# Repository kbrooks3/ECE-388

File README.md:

# ECE-388
Ping Pong Balancer Project
LCDScreen actually has all of the code included, I'm just lazy about renaming it.
If anyone wants to redefine stuff or change how things are that's probably fine,
I'm not committed to anything really.

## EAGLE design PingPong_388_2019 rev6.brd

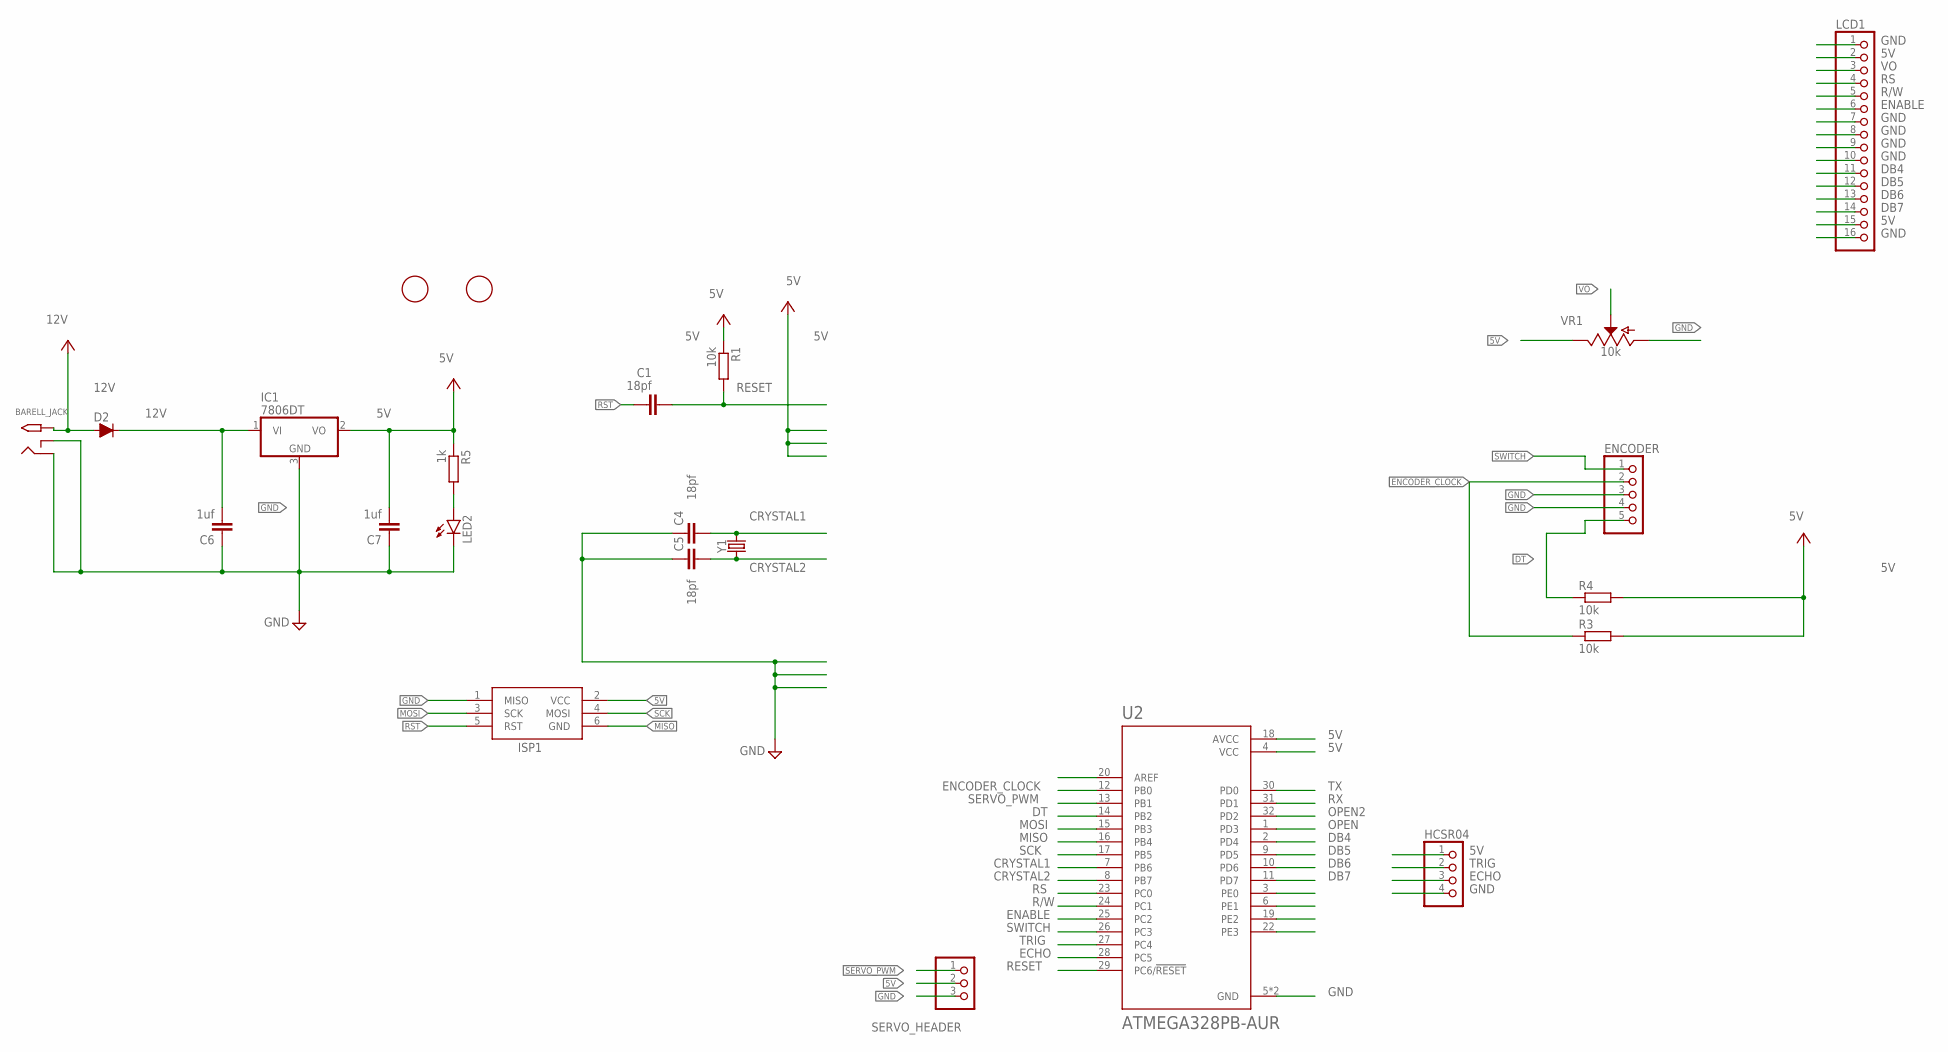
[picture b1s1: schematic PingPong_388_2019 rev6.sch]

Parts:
BARELL_JACK: 2.1MMJACKTHM; PJ-102A
C1, C4, C5: 18pf; C0805
C6, C7: 1uf; C0805
D2: D-FILL-MLL-34; MELF-MLL34
ENCODER: PINHD-1X5; 1X05
HCSR04: PINHD-1X4; 1X04
IC1: 7806DT; TO252
ISP1: AVRISP-6; AVRISP
LCD1: PINHD-1X16; 1X16
LED2: LEDSML0805; SML0805
R1, R3, R4: 10k; R0805
R5: 1k; R0805
SERVO_HEADER: PINHD-1X3; 1X03
U2: ATMEGA328PB-AUR; QFP80P900X900X120-32N
U$3, U$4: FIDUCIAL; FIDUCIAL_1MM
VR1: 10k; POT-PTH-ALPS
Y1: CRYSTALSMD-HC49UP; HC49UP

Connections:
5V: C7.2, HCSR04.1, IC1.2 (VO), ISP1.2 (VCC), LCD1.2, LCD1.15, R1.1, R3.2, R4.2, R5.1, SERVO_HEADER.2, U2.4 (VCC), U2.18 (AVCC), VR1.P$1 (E)
12V: BARELL_JACK.TIP, C6.2, D2.1 (C), D2.2 (A), IC1.1 (VI)
CRYSTAL1: C4.2, U2.7 (PB6), Y1.2
CRYSTAL2: C5.2, U2.8 (PB7), Y1.1
DB4: LCD1.11, U2.2 (PD4)
DB5: LCD1.12, U2.9 (PD5)
DB6: LCD1.13, U2.10 (PD6)
DB7: LCD1.14, U2.11 (PD7)
DT: ENCODER.5, R4.1, U2.14 (PB2)
ECHO: HCSR04.3, U2.28 (PC5)
ENABLE: LCD1.6, U2.25 (PC2)
ENCODER_CLOCK: ENCODER.2, R3.1, U2.12 (PB0)
GND: BARELL_JACK.RING, BARELL_JACK.RING_SW, C4.1, C5.1, C6.1, C7.1, ENCODER.3, ENCODER.4, HCSR04.4, IC1.3 (GND), ISP1.1 (MISO), LCD1.1, LCD1.7, LCD1.8, LCD1.9, LCD1.10, LCD1.16, LED2.C, SERVO_HEADER.3, U2.5 (GND), U2.21 (GND), VR1.P$3 (A)
MISO: ISP1.6 (GND), U2.16 (PB4)
MOSI: ISP1.3 (SCK), U2.15 (PB3)
unnamed: LED2.A, R5.2
OPEN: U2.1 (PD3)
OPEN2: U2.32 (PD2)
R/W: LCD1.5, U2.24 (PC1)
RESET: C1.2, R1.2, U2.29 (PC6/!RESET)
RS: LCD1.4, U2.23 (PC0)
RST: C1.1, ISP1.5 (RST)
RX: U2.31 (PD1)
SCK: ISP1.4 (MOSI), U2.17 (PB5)
SERVO_PWM: SERVO_HEADER.1, U2.13 (PB1)
SWITCH: ENCODER.1, U2.26 (PC3)
TRIG: HCSR04.2, U2.27 (PC4)
TX: U2.30 (PD0)
VO: LCD1.3, VR1.P$2 (S)

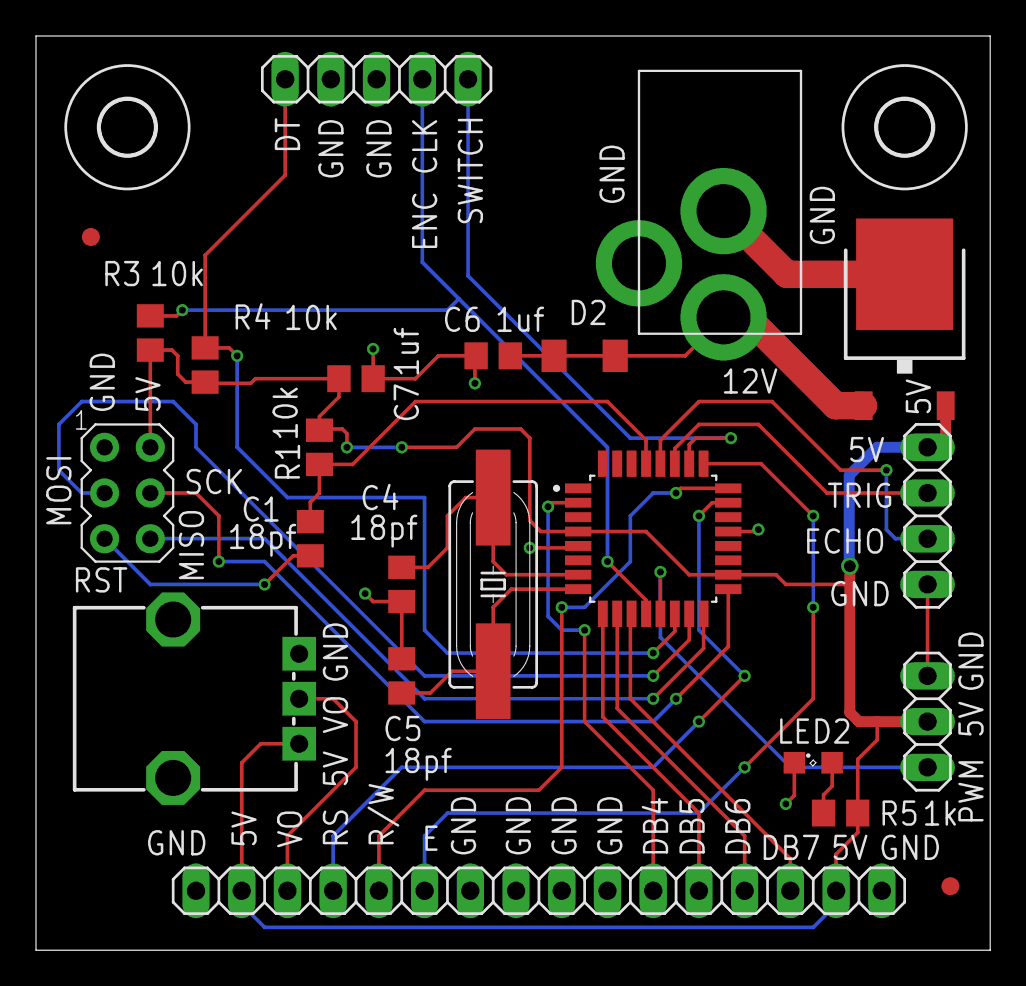
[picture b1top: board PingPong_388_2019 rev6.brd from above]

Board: 2 copper layers, 53.0 x 50.8 mm, 25 parts (0 on the bottom side), 25 nets.

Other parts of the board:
U$1, U$2: 3,0

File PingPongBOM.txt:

Partlist exported from //umdfs1.umdar.umassd.edu/studentshares$/jdalzell/Downloads/PingPong_388_2019 rev2.sch at 11/5/2019 3:35 PM

Part         Value           Device                          Package               Description                                                                              AVAILABILITY DESCRIPTION          MF             MP         PACKAGE      POPULARITY PRICE     PROD_ID         SF_SKU            SPICEPREFIX VALUE
BARELL_JACK  2.1MMJACKTHM    2.1MMJACKTHM                    PJ-102A               2.1mm x 5.5mm THM DC jack with internal switch. Digikey part #PJ-102A, 4UCON part #05537                                                                                                                                                  
C1           18pf            C-EUC0805                       C0805                 CAPACITOR, European symbol                                                                                                                                        88                                                     C                
C4           18pf            C-EUC0805                       C0805                 CAPACITOR, European symbol                                                                                                                                        88                                                     C                
C5           18pf            C-EUC0805                       C0805                 CAPACITOR, European symbol                                                                                                                                        88                                                     C                
C6                           C-EUC0805                       C0805                 CAPACITOR, European symbol                                                                                                                                        88                                                     C                
C7                           C-EUC0805                       C0805                 CAPACITOR, European symbol                                                                                                                                        88                                                     C                
D2                           D-FILL-MLL-34                   MELF-MLL34            DIODE                                                                                                                                                             0                                                                       
HCSR04                       PINHD-1X4                       1X04                  PIN HEADER                                                                                                                                                        91                                                                      
IC1          7805T           7805T                           TO220H                Positive VOLTAGE REGULATOR                                                                                                                                                                                                                
ISP1         AVRISP-6        AVRISP-6                        AVRISP                AVR ISP HEADER                                                                                                                                                                                                                            
LCD1                         PINHD-1X16                      1X16                  PIN HEADER                                                                                                                                                        17                                                                      
LED2                         LED                             SMARTLED-TTW          LED                                                                                                                                                               3                                                                       
R1           10k             R-EU_R0805                      R0805                 RESISTOR, European symbol                                                                                                                                         86                                                     R                
R3           10k             R-EU_R0805                      R0805                 RESISTOR, European symbol                                                                                                                                         86                                                     R                
R4           10k             R-EU_R0805                      R0805                 RESISTOR, European symbol                                                                                                                                         86                                                     R                
R5           1k              R-EU_R0805                      R0805                 RESISTOR, European symbol                                                                                                                                         86                                                     R                
S1           ENCODER-SWITCH  ENCODER-SWITCH                  ROTARY_ENC_PLAIN      Rotary Encoder w/ Select Switch                                                                                                                                                                        COM-09117                          
SERVO_HEADER                 PINHD-1X3                       1X03                  PIN HEADER                                                                                                                                                        92                                                                      
U2           ATMEGA328PB-AUR ATMEGA328PB-AUR                 QFP80P900X900X120-32N ATmega Series 20 MHz 32 KB Flash 2 KB SRAM 8-Bit Microcontroller - TQFP-32               Unavailable   AVR microcontroller  EEPROM: 1024B  SRAM: 2kB  Flash: 32kB  TQFP32    Microchip ATMEGA328PB-AUR TQFP-32 Microchip             None 
VR1          10k             POTENTIOMETER-PTH-9MM-1/20W-20% POT-PTH-ALPS          Potentiometer (Pot)                                                                                                                                                                    RES-09177       COM-09288                     10k  
Y1                           CRYSTALSMD-HC49UP               HC49UP                Crystals (Generic)

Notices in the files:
parts and their libraries:
SparkFun-Resistors: Licensing: Creative Commons ShareAlike 4.0 International - https://creativecommons.org/licenses/by-sa/4.0
